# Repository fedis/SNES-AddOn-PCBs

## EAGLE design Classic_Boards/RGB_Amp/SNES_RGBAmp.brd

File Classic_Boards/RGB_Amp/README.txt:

Solder Joints:

R - red image component from S-CPUN pin156
G - green image component from S-CPUN pin157
B - blue image component from S-CPUN pin158

solder PCB directly beneath the MultiAV
deactivate the RGB-output of S-RGB by lifting pin20, 22 and 24 from mainboard
installation guide: http://retrorgb.com/1chiprgb.html

-----------------------------------------------------------------------------------

Values of passive components (all 0805 packages):

R1 - R3: 75Ohm (100Ohm is also possible and gives a darker image but is a bit dirty; use resitors at the input instead)
C1     : 0.1uF

-----------------------------------------------------------------------------------

Active IC (SOIC8 packages):

THS7314: for more information see ti.com (THS7316 is also applicable to use)

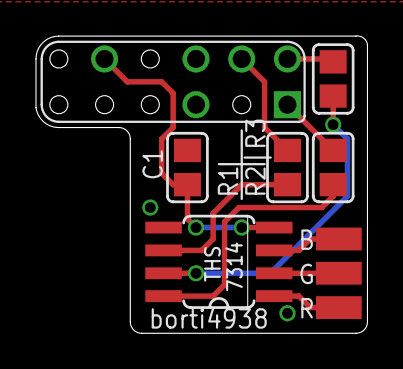
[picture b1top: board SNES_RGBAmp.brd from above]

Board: 2 copper layers, 18.4 x 16.5 mm, 9 parts (0 on the bottom side), 11 nets.

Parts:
B: SMD1,27-2,54
C1: 100n; Z0805
G: SMD1,27-2,54
R: SMD1,27-2,54
R1, R2, R3: 100; Z0805
U$1: THS7314
U$3: SNES_MULTIAV_RGB_ONLY

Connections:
GND: C1.2, U$1.5, U$3.P$5, U$3.P$6
unnamed: R.1, U$1.1
unnamed: G.1, U$1.2
unnamed: B.1, U$1.3
unnamed: R2.1, U$1.8
unnamed: R2.2, U$3.P$1
unnamed: R3.2, U$3.P$2
unnamed: R3.1, U$1.7
unnamed: R1.1, U$1.6
unnamed: R1.2, U$3.P$4
VCC: C1.1, U$1.4, U$3.P$10

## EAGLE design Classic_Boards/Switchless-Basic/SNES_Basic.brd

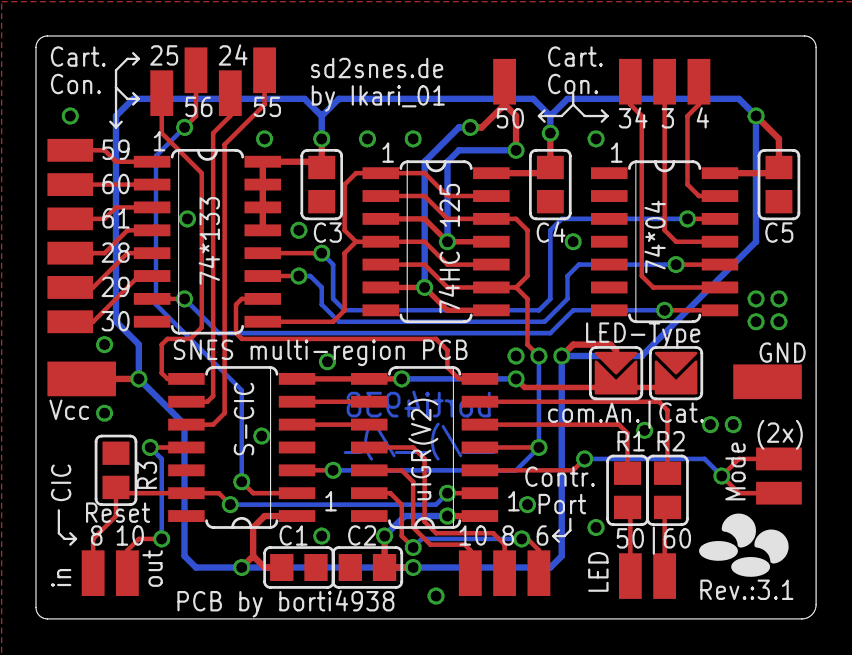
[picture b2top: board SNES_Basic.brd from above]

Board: 2 copper layers, 43.3 x 32.4 mm, 40 parts (0 on the bottom side), 35 nets.

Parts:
74*04, 74HC(T)125: SO14
74*133: SO16
C1, C2, C3, C4, C5: C100n; Z0805
CIC1, CIC2, CIC7, CIC8, CIC10, CIC11: SMD1,27-2,54
CPP2, CPP3, CPP4: SMD1,27-2,54
D4: SMD1,27-2,54
LED_NTSC: SMD1,27-2,54
LED_PAL: SMD1,27-2,54
MODE, MODE1: SMD1,27-2,54
PAD13, PAD14, PAD15, PAD16, PAD17, PAD18, PAD19, PAD20, PAD21: SMD1,27-2,54
PAD_GND: PADS
PAD_VCC: PADS
R1: R10k; Z0805
R2, R3: R220; Z0805
U$2, U$3: PIC16F630_SIMPLE; PIC16F630
U$4, U$5: MY_JUMPER; MYJUMP

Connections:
D4_ON/OFF: 74*133.10, U$3.7
GND: 74*04.3, 74*04.5, 74*04.7, 74*133.8, 74HC(T)125.7, C1.2, C2.2, C3.2, C4.2, C5.2, PAD_GND.P$1, R1.1, U$2.4, U$2.14, U$3.14, U$5.P$1
unnamed: LED_PAL.1, R2.2
unnamed: 74*133.9, 74HC(T)125.1, 74HC(T)125.4, 74HC(T)125.10, 74HC(T)125.13
unnamed: CIC10.1, U$2.11
unnamed: 74*133.5, PAD17.1
unnamed: 74*133.4, PAD16.1
unnamed: 74*133.3, PAD19.1
unnamed: 74*133.2, PAD20.1
unnamed: 74*133.1, PAD21.1
unnamed: CIC7.1, U$2.2
unnamed: CIC8.1, R1.2, U$2.13, U$3.2
unnamed: 74*04.9, PAD13.1
unnamed: R2.1, U$3.5
unnamed: R3.1, U$3.6
unnamed: LED_NTSC.1, R3.2
unnamed: 74*133.6, PAD18.1
unnamed: 74*04.8, 74*133.7
unnamed: 74*04.10, 74*133.11
unnamed: 74*04.13, PAD15.1
unnamed: U$2.5, U$3.10
unnamed: 74*04.12, 74*133.12
unnamed: 74*04.11, PAD14.1
unnamed: CPP2.1, U$3.11
unnamed: CPP3.1, U$3.12
unnamed: 74HC(T)125.3, 74HC(T)125.6, 74HC(T)125.8, 74HC(T)125.11, D4.1
unnamed: CPP4.1, U$3.13
unnamed: CIC1.1, U$2.10
unnamed: CIC2.1, U$2.9
unnamed: CIC11.1, U$2.8
unnamed: U$2.6, U$3.9
unnamed: U$2.7, U$3.8, U$4.P$2, U$5.P$2
unnamed: MODE.1, MODE1.1, U$3.3
UIGR: 74HC(T)125.2, 74HC(T)125.5, 74HC(T)125.9, 74HC(T)125.12, U$2.3, U$3.4
VCC: 74*04.14, 74*133.13, 74*133.14, 74*133.15, 74*133.16, 74HC(T)125.14, C1.1, C2.1, C3.1, C4.1, C5.1, PAD_VCC.P$1, U$2.1, U$3.1, U$4.P$1

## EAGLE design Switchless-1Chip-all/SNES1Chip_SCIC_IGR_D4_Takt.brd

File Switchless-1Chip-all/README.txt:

As produced for communities:
- Circuit-Board.de
- SNES-Projects.de
- snesfreaks.com

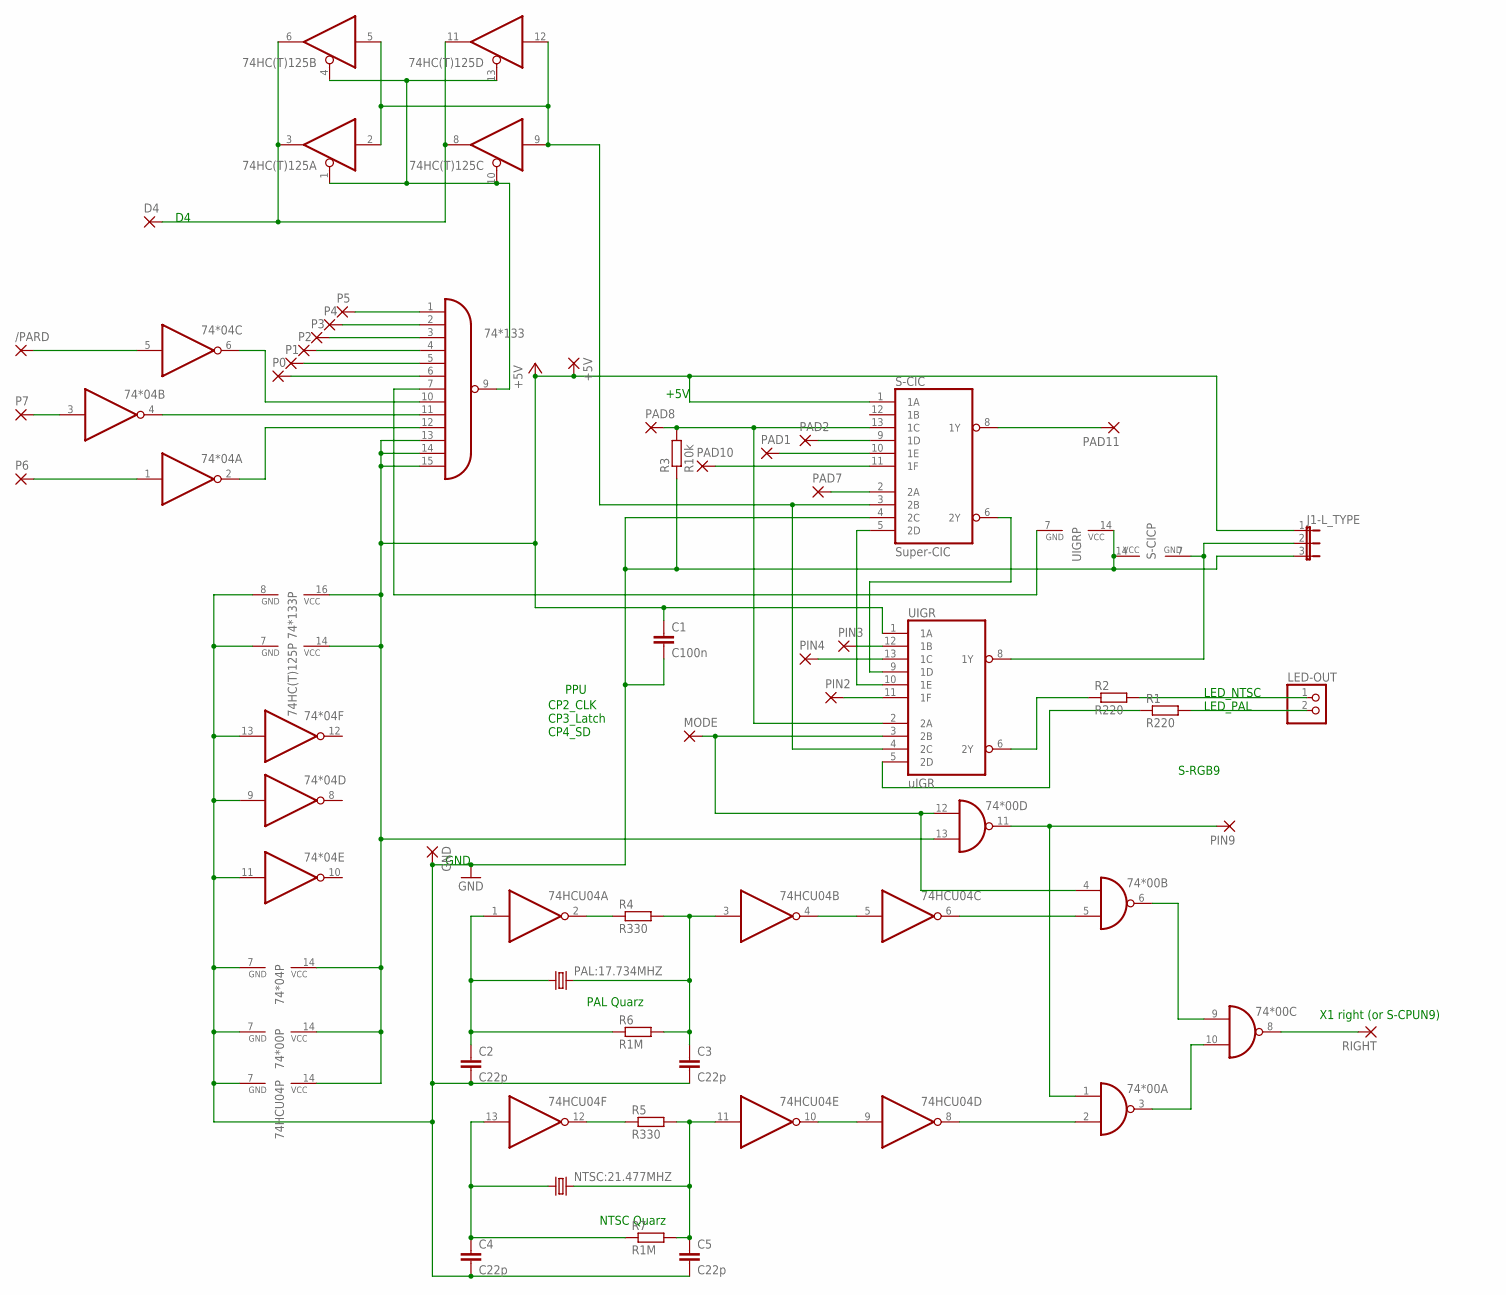
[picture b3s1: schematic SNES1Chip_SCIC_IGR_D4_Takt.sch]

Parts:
74*00: 7400D; SO14
74*04: 74S04D; SO14
74*133: 74S133D; SO16
74HC(T)125: 74HCT125D; SO14
74HCU04: 74HC04D; SO14
+5V: 2,54/0,8
/PARD: 2,54/0,8
C1: C100n; C0805
C2, C3, C4, C5: C22p; C0805
D4: 2,54/0,8
GND: 2,54/0,8
J1-L_TYPE: JP2E; JP2
LED-OUT: PINHD-1X2; 1X02
MODE: 2,54/0,8
NTSC:21.477MHZ: CRYSTALHC49S; HC49/S
P0, P1, P2, P3, P4, P5, P6, P7: 2,54/0,8
PAD1, PAD2, PAD7, PAD8, PAD10, PAD11: 2,54/0,8
PAL:17.734MHZ: CRYSTALHC49S; HC49/S
PIN2, PIN3, PIN4, PIN9: 2,54/0,8
R1, R2: R220; R0805
R3: R10k; R0805
R4, R5: R330; R0805
R6, R7: R1M; R0805
RIGHT: 2,54/0,8
S-CIC: Super-CIC; SO14
UIGR: uIGR; SO14

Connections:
+5V: 74*00.13 (I1), 74*00.14 (VCC), 74*04.14 (VCC), 74*133.13 (I10), 74*133.14 (I11), 74*133.15 (I12), 74*133.16 (VCC), 74HC(T)125.14 (VCC), 74HCU04.14 (VCC), +5V.1, C1.1, J1-L_TYPE.1, S-CIC.1 (1A), UIGR.1 (1A)
GND: 74*00.7 (GND), 74*04.7 (GND), 74*04.9 (I), 74*04.11 (I), 74*04.13 (I), 74*133.8 (GND), 74HC(T)125.7 (GND), 74HCU04.7 (GND), C1.2, C2.2, C3.2, C4.2, C5.2, GND.1, J1-L_TYPE.3, R3.1, S-CIC.4 (2C), S-CIC.14 (VCC), UIGR.14 (VCC)
unnamed: 74*04.4 (O), 74*133.11 (I8)
unnamed: 74*133.9 (O), 74HC(T)125.1 (OE), 74HC(T)125.4 (OE), 74HC(T)125.10 (OE), 74HC(T)125.13 (OE)
unnamed: PAD10.1, S-CIC.11 (1F)
unnamed: PAD11.1, S-CIC.8 (1Y)
unnamed: LED-OUT.1, R2.2
unnamed: 74*04.1 (I), P6.1
unnamed: R2.1, UIGR.6 (2Y)
unnamed: J1-L_TYPE.2, S-CIC.7 (GND), UIGR.8 (1Y)
unnamed: 74*04.6 (O), 74*133.10 (I7)
unnamed: PAD7.1, S-CIC.2 (2A)
unnamed: R1.1, UIGR.5 (2D)
unnamed: PAD2.1, S-CIC.9 (1D)
unnamed: PAD1.1, S-CIC.10 (1E)
unnamed: LED-OUT.2, R1.2
unnamed: 74*133.6 (I5), P0.1
unnamed: 74*04.3 (I), P7.1
unnamed: PIN2.1, UIGR.11 (1F)
unnamed: PIN3.1, UIGR.12 (1B)
unnamed: PIN4.1, UIGR.13 (1C)
unnamed: 74*04.2 (O), 74*133.12 (I9)
unnamed: 74*133.1 (I0), P5.1
unnamed: 74*133.2 (I1), P4.1
unnamed: S-CIC.6 (2Y), UIGR.9 (1D)
unnamed: 74*133.3 (I2), P3.1
unnamed: 74*133.4 (I3), P2.1
unnamed: 74*04.5 (I), /PARD.1
unnamed: 74HCU04.1 (I), C2.1, PAL:17.734MHZ.1, R6.1
unnamed: 74HCU04.3 (I), C3.1, PAL:17.734MHZ.2, R4.2, R6.2
unnamed: 74HCU04.13 (I), C4.1, NTSC:21.477MHZ.1, R7.1
unnamed: 74HCU04.11 (I), C5.1, NTSC:21.477MHZ.2, R5.2, R7.2
unnamed: 74*00.3 (O), 74*00.10 (I1)
unnamed: 74*00.6 (O), 74*00.9 (I0)
unnamed: 74*00.4 (I0), 74*00.12 (I0), MODE.1, UIGR.3 (2B)
unnamed: PAD8.1, R3.2, S-CIC.13 (1C), UIGR.2 (2A)
unnamed: 74*00.1 (I0), 74*00.11 (O), PIN9.1
unnamed: 74*00.8 (O), RIGHT.1
unnamed: 74HCU04.2 (O), R4.1
unnamed: 74HCU04.4 (O), 74HCU04.5 (I)
unnamed: 74*00.5 (I1), 74HCU04.6 (O)
unnamed: 74*133.5 (I4), P1.1
unnamed: 74*00.2 (I1), 74HCU04.8 (O)
unnamed: 74HC(T)125.3 (O), 74HC(T)125.6 (O), 74HC(T)125.8 (O), 74HC(T)125.11 (O), D4.1
unnamed: 74*133.7 (I6), UIGR.7 (GND)
unnamed: 74HCU04.9 (I), 74HCU04.10 (O)
unnamed: 74HCU04.12 (O), R5.1
unnamed: S-CIC.5 (2D), UIGR.10 (1E)
UIGR: 74HC(T)125.2 (I), 74HC(T)125.5 (I), 74HC(T)125.9 (I), 74HC(T)125.12 (I), S-CIC.3 (2B), UIGR.4 (2C)

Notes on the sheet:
PPU
+5V
GND
CP2_CLK CP3_Latch CP4_SD
PAL Quarz
NTSC Quarz
S-RGB9
X1 right (or S-CPUN9)
LED_NTSC LED_PAL

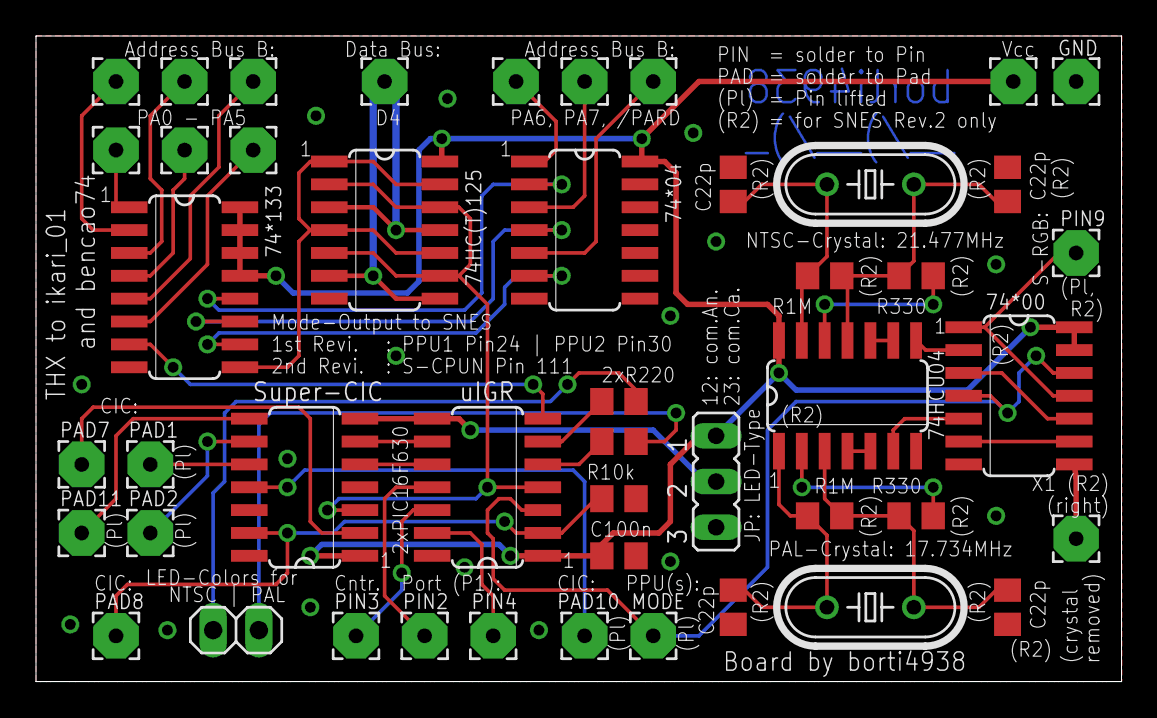
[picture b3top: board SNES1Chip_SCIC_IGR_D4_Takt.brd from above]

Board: 2 copper layers, 60.3 x 35.9 mm, 47 parts (0 on the bottom side), 49 nets.

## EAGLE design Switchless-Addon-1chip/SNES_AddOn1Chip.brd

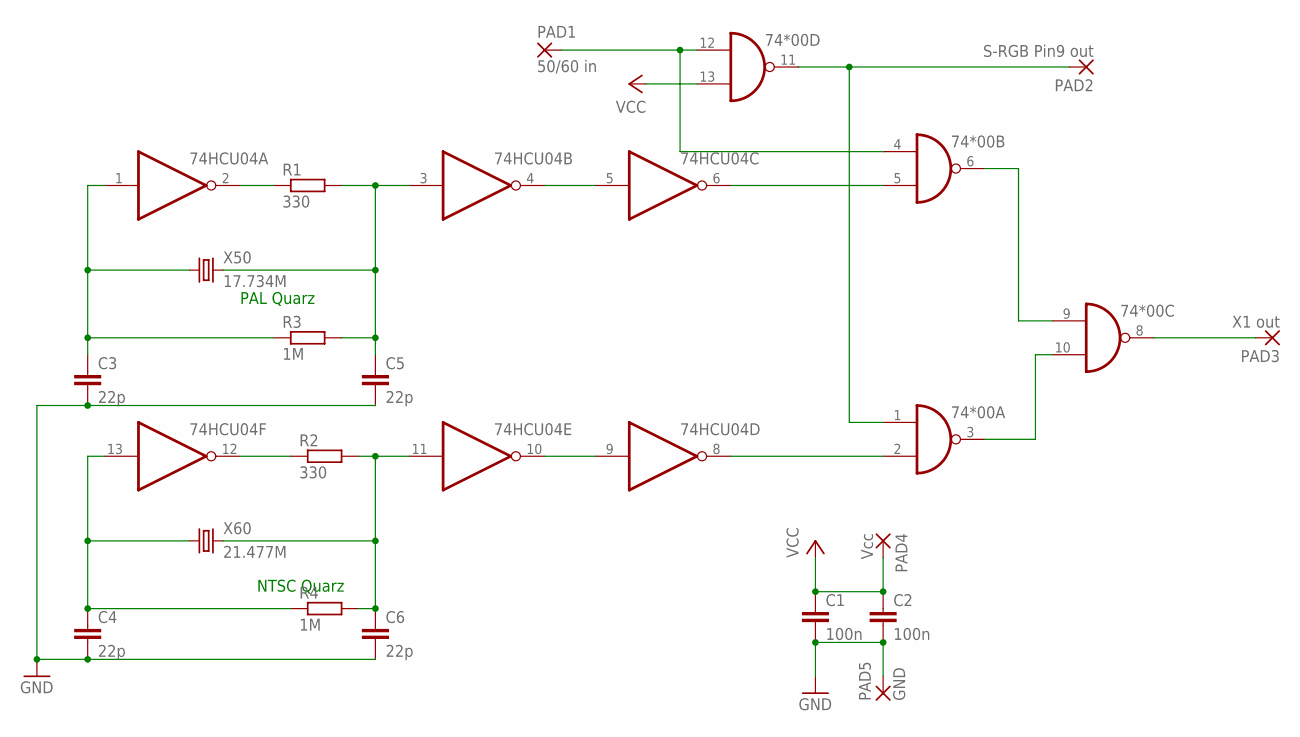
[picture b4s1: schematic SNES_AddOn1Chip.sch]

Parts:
74*00: 7400D; SO14
74HCU04: 74HC04D; SO14
C1, C2: 100n; Z0805
C3, C4, C5, C6: 22p; Z0805
PAD1: 50/60 in; SMD1,27-2,54
PAD2: S-RGB Pin9 out; SMD1,27-2,54
PAD3: X1 out; SMD1,27-2,54
PAD4: Vcc; SMD2,54-5,08
PAD5: GND; SMD2,54-5,08
R1, R2: 330; Z0805
R3, R4: 1M; Z0805
X50: 17.734M; HC49/S
X60: 21.477M; HC49/S

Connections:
GND: 74*00.7 (GND), 74HCU04.7 (GND), C1.2, C2.2, C3.2, C4.2, C5.2, C6.2, PAD5.1
unnamed: 74HCU04.1 (I), C3.1, R3.1, X50.1
unnamed: 74HCU04.3 (I), C5.1, R1.2, R3.2, X50.2
unnamed: 74HCU04.13 (I), C4.1, R4.1, X60.1
unnamed: 74HCU04.11 (I), C6.1, R2.2, R4.2, X60.2
unnamed: 74*00.3 (O), 74*00.10 (I1)
unnamed: 74*00.6 (O), 74*00.9 (I0)
unnamed: 74*00.4 (I0), 74*00.12 (I0), PAD1.1
unnamed: 74*00.1 (I0), 74*00.11 (O), PAD2.1
unnamed: 74*00.8 (O), PAD3.1
unnamed: 74HCU04.2 (O), R1.1
unnamed: 74HCU04.4 (O), 74HCU04.5 (I)
unnamed: 74*00.5 (I1), 74HCU04.6 (O)
unnamed: 74*00.2 (I1), 74HCU04.8 (O)
unnamed: 74HCU04.9 (I), 74HCU04.10 (O)
unnamed: 74HCU04.12 (O), R2.1
VCC: 74*00.13 (I1), 74*00.14 (VCC), 74HCU04.14 (VCC), C1.1, C2.1, PAD4.1

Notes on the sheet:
PAL Quarz
NTSC Quarz

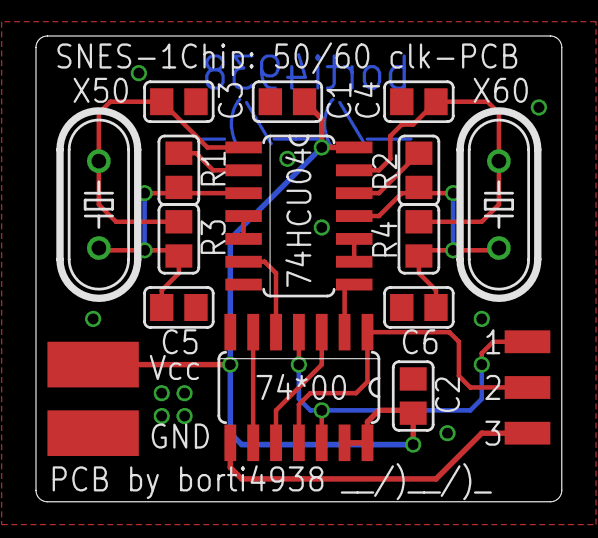
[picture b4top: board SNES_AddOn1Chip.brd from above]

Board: 2 copper layers, 29.2 x 25.9 mm, 19 parts (0 on the bottom side), 17 nets.
